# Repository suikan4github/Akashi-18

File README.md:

# Akashi-18
Pico Trainer : Raspberry Pi Pico board with full color LED.

# Details
To provide much fan for the first-day trainee, using full color LED. 

The PCB employs followings : 
Parts              | QTY
-------------------|-----
Full Color LED     | 1
Push button Switch | 3
Potentiometer      | 1

The following table shows the pin connections. 

Color | GPIO 
------|--------
Red   | 20
Green | 21
Blue  | 22

Each GPIO is active Hi. That means, 
Output "H" signal to turn on the LED.

There are three user switches : 

Switch | GPIO
-------|------
SW1    | 11
SW2    | 12
SW3    | 13

All switches are active Lo. That means, pushing down the switch makes
the GPIO input to "L". 

The potentiometer is connected to ADC0. 

# Additional documents
- [Schematics](doc/Akashi-18.pdf)
- [Parts list](doc/partslist.ods)

# Gallery

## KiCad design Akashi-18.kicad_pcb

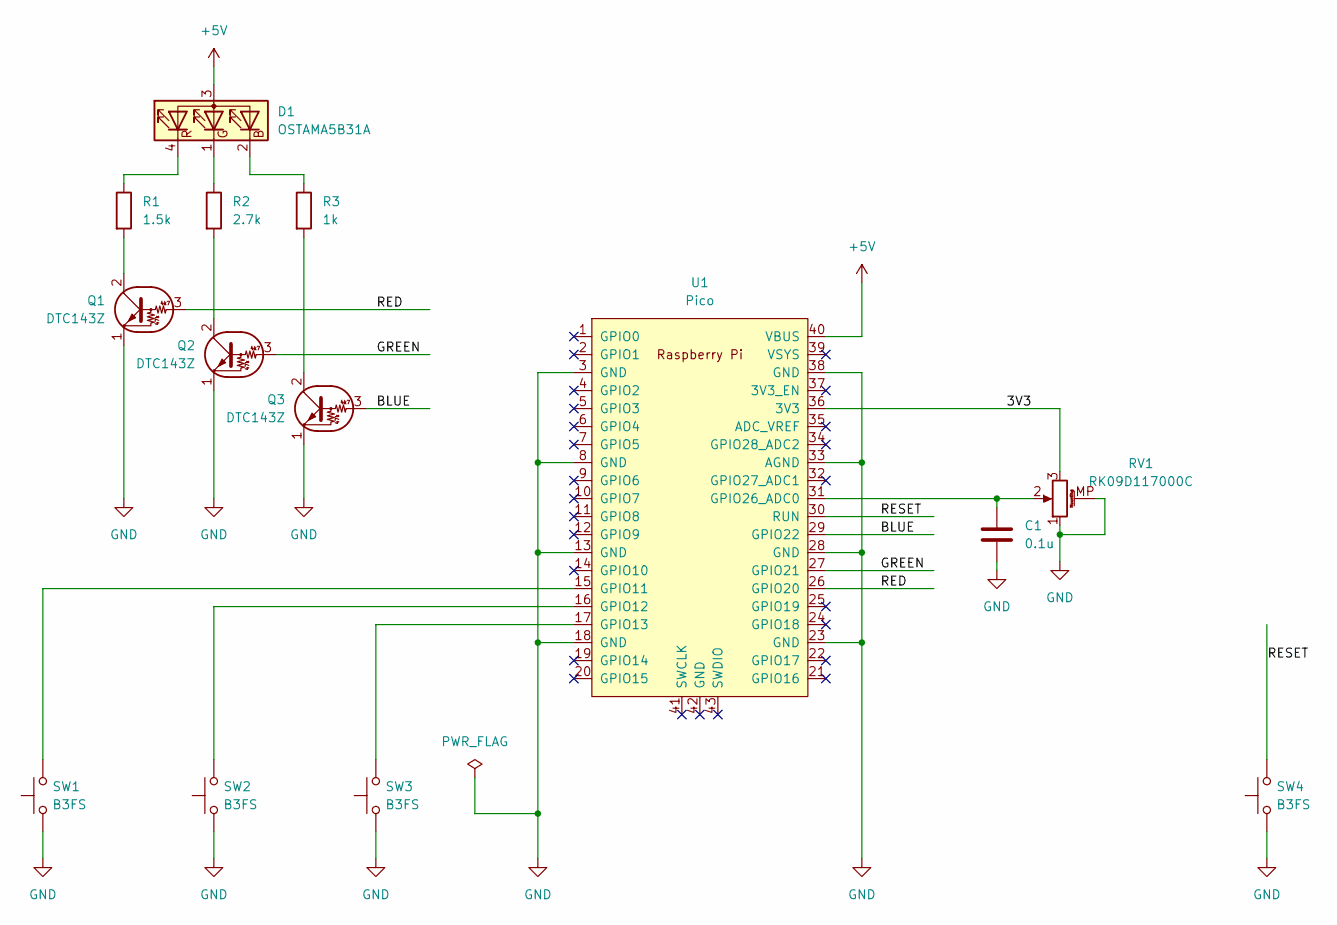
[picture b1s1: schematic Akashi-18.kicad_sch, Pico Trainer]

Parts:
C1: 0.1u; C_Disc_D8.0mm_W2.5mm_P5.00mm
D1: OSTAMA5B31A; LED_D5.0mm-4_RGB
Q1, Q2, Q3: DTC143Z; TO-92_Inline
R1: 1.5k; R_Axial_DIN0207_L6.3mm_D2.5mm_P10.16mm_Horizontal
R2: 2.7k; R_Axial_DIN0207_L6.3mm_D2.5mm_P10.16mm_Horizontal
R3: 1k; R_Axial_DIN0207_L6.3mm_D2.5mm_P10.16mm_Horizontal
RV1: RK09D117000C; Potentiometer_Alps_RK09K_Single_Vertical
SW1, SW2, SW3, SW4: B3FS; SW_TH_Tactile_Omron_B3F-10xx
U1: Pico; RPi_Pico_SMD_TH

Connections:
+5V: D1.3 (A), U1.40 (VBUS)
/3V3: RV1.3, U1.36 (3V3)
/BLUE: Q3.3 (B), U1.29 (GPIO22)
/GREEN: Q2.3 (B), U1.27 (GPIO21)
/RED: Q1.3 (B), U1.26 (GPIO20)
/RESET: SW4.2, U1.30 (RUN)
GND: C1.2, Q1.1 (E), Q2.1 (E), Q3.1 (E), RV1.1, RV1.MP (MountPin), SW1.1, SW2.1, SW3.1, SW4.1, U1.3 (GND), U1.8 (GND), U1.13 (GND), U1.18 (GND), U1.23 (GND), U1.28 (GND), U1.33 (AGND), U1.38 (GND)
unnamed: D1.2 (BK), R3.1
unnamed: D1.1 (GK), R2.1
unnamed: D1.4 (RK), R1.1
unnamed: Q1.2 (C), R1.2
unnamed: Q2.2 (C), R2.2
unnamed: Q3.2 (C), R3.2
unnamed: SW1.2, U1.15 (GPIO11)
unnamed: SW2.2, U1.16 (GPIO12)
unnamed: SW3.2, U1.17 (GPIO13)
unnamed: C1.1, RV1.2, U1.31 (GPIO26_ADC0)

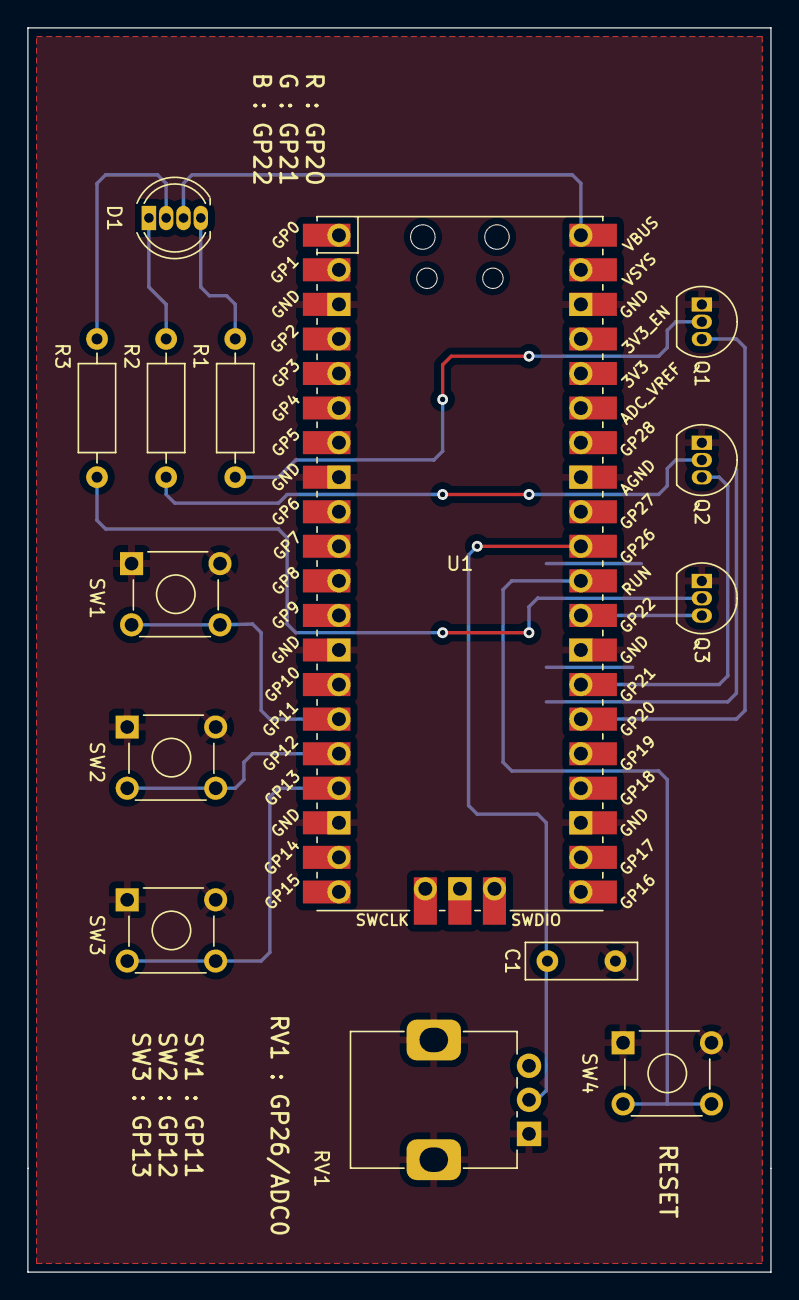
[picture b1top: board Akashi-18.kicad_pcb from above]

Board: 2 copper layers, 54.6 x 91.4 mm, 14 parts (0 on the bottom side), 17 nets.

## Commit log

2023-12-18 Place initial parts
2023-12-19 Layout done
2023-12-19 All modified parts are registered to the local lib.
2023-12-19 Adjust the space of transistor.
2023-12-19 Add capacitor
    For RF Immunity reduction.
    Also added parts list.
2023-12-20 Reshaped to the business card size.
2023-12-20 Refine the size and placement.
2023-12-23 Correct the parts list and refine the PCB layout.
    Volume -> A-curve.
    RasPi Pico -> wo Header.
    Connector -> Conthrough.
    PCB layout has been refined for the better visibility of the
    RV1 comment.
2023-12-23 Update README.
    Added Schematics PDF.
2023-12-23 Add gerber file.
2023-12-23 Correct the parts qty of the connector.
2024-01-06 Change resitor value to good for the education.
    - Update parts list.
    - Added assembled board photo.
2024-01-17 Add reset switch.
2024-01-17 Gerber generated
